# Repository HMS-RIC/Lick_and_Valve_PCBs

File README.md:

# Lick Sensor and Valve Driver PCBs

Two useful PCBs:

- A two channel resistive lick sensor.

- An eight channel valve driver with the option of automatic operation with a microcontroller (Teensy).

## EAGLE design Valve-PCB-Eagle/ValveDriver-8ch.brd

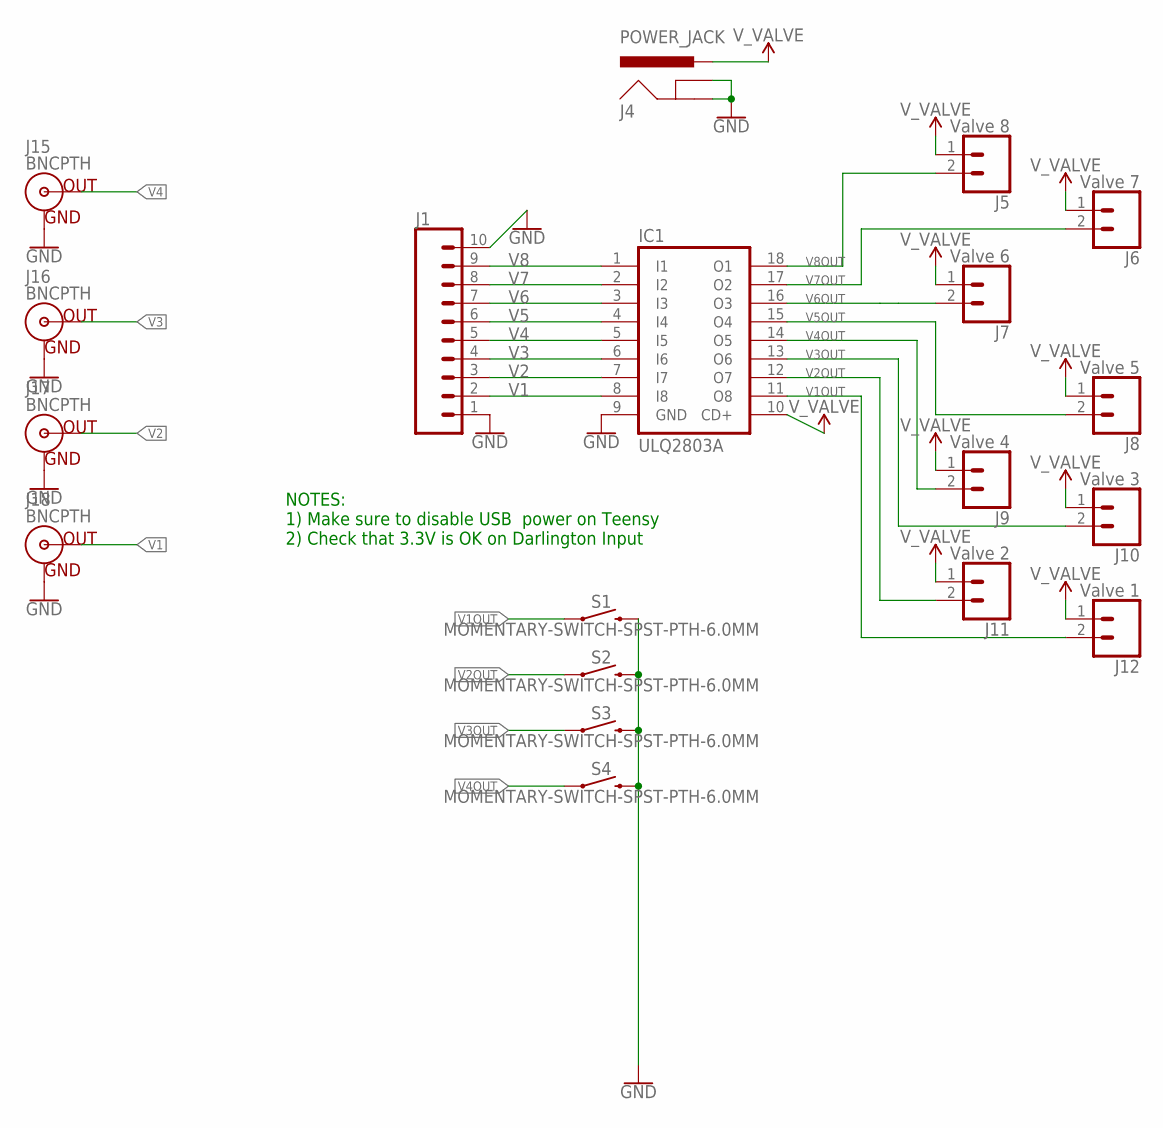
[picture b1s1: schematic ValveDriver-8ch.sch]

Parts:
IC1: ULQ2803A; DIL18
J1: CONN_10"; 1X10
J4: POWER_JACK; POWER_JACK_PTH
J5: Valve 8; 1X02
J6: Valve 7; 1X02
J7: Valve 6; 1X02
J8: Valve 5; 1X02
J9: Valve 4; 1X02
J10: Valve 3; 1X02
J11: Valve 2; 1X02
J12: Valve 1; 1X02
J15, J16, J17, J18: BNCPTH; BNC
S1, S2, S3, S4: MOMENTARY-SWITCH-SPST-PTH-6.0MM; TACTILE_SWITCH_PTH_6.0MM

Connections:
GND: IC1.9 (GND), J1.1, J1.10, J4.GND, J4.GNDBREAK, J15.GND, J16.GND, J17.GND, J18.GND, S1.3 (2), S2.3 (2), S3.3 (2), S4.3 (2)
V1: IC1.8 (I8), J1.2, J18.S (OUT)
V1OUT: IC1.11 (O8), J12.2, S1.1
V2: IC1.7 (I7), J1.3, J17.S (OUT)
V2OUT: IC1.12 (O7), J11.2, S2.1
V3: IC1.6 (I6), J1.4, J16.S (OUT)
V3OUT: IC1.13 (O6), J10.2, S3.1
V4: IC1.5 (I5), J1.5, J15.S (OUT)
V4OUT: IC1.14 (O5), J9.2, S4.1
V5: IC1.4 (I4), J1.6
V5OUT: IC1.15 (O4), J8.2
V6: IC1.3 (I3), J1.7
V6OUT: IC1.16 (O3), J7.2
V7: IC1.2 (I2), J1.8
V7OUT: IC1.17 (O2), J6.2
V8: IC1.1 (I1), J1.9
V8OUT: IC1.18 (O1), J5.2
V_VALVE: IC1.10 (CD+), J4.PWR, J5.1, J6.1, J7.1, J8.1, J9.1, J10.1, J11.1, J12.1

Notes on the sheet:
NOTES: 1) Make sure to disable USB power on Teensy 2) Check that 3.3V is OK on Darlington Input

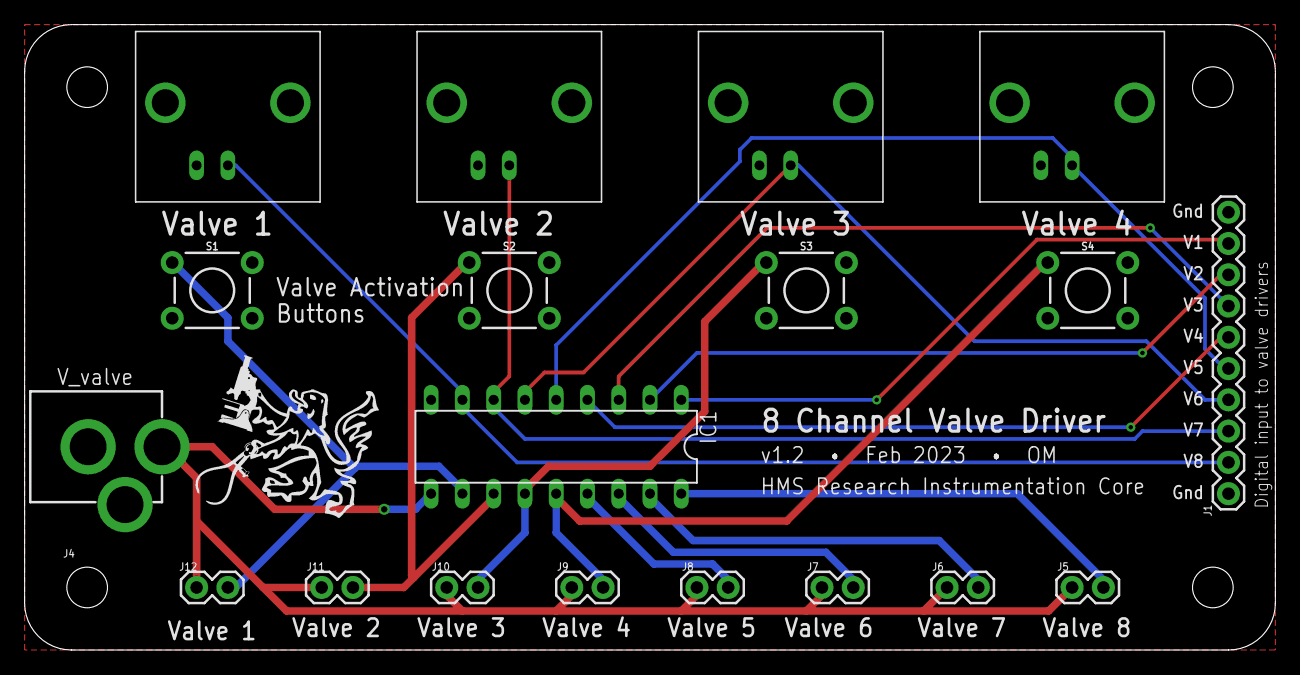
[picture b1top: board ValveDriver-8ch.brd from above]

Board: 2 copper layers, 101.6 x 50.8 mm, 24 parts (0 on the bottom side), 18 nets.

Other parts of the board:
U$2, U$4, U$5, U$6: STAND-OFF
U$7: RIC_LOGO_BIG

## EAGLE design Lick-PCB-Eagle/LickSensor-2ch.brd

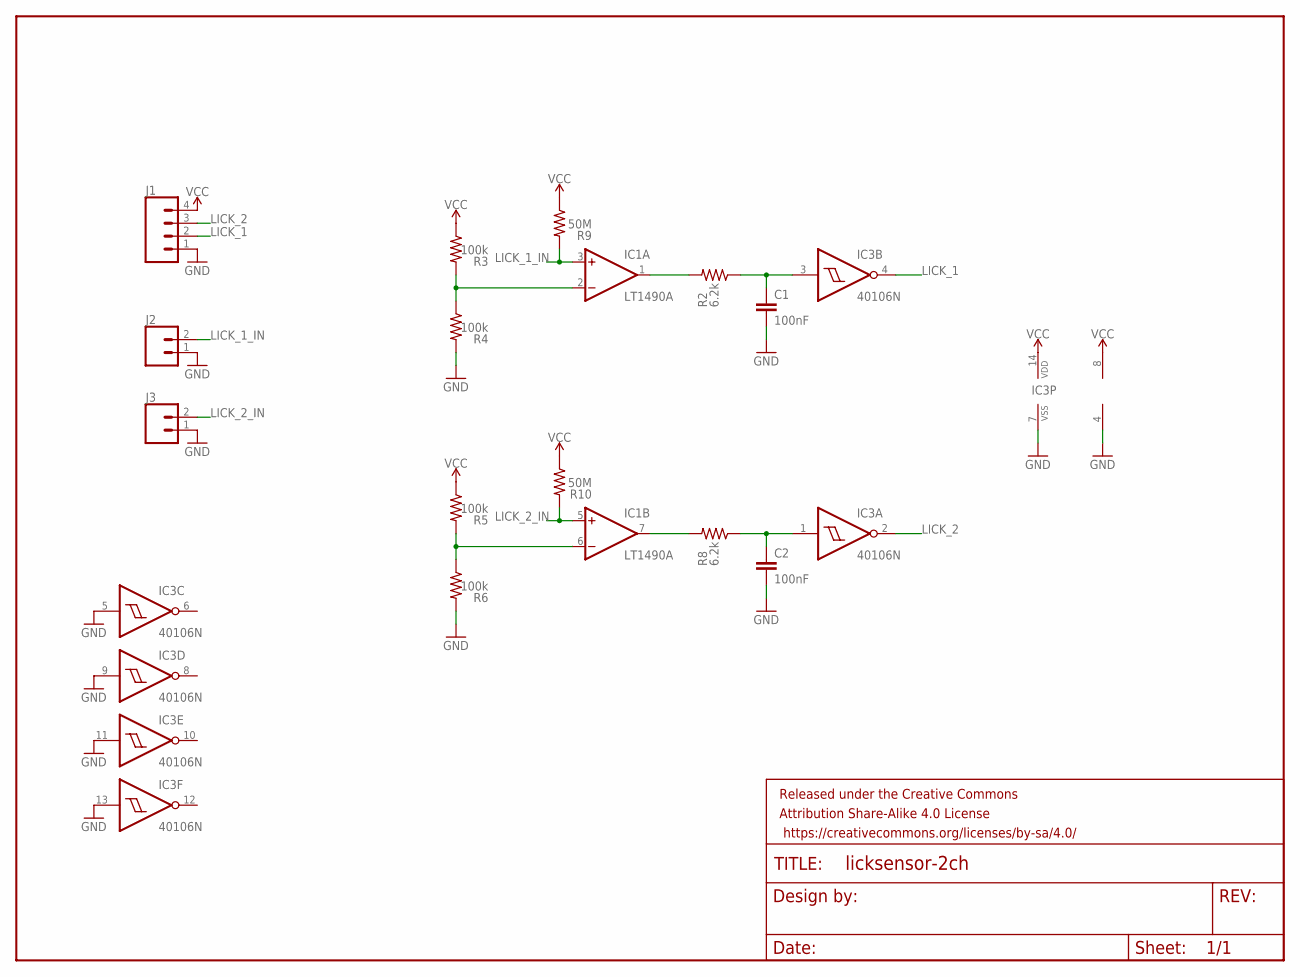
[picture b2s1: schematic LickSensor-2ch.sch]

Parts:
C1, C2: 100nF; C5B3
FRAME1: FRAME-LETTER; CREATIVE_COMMONS
IC1: LT1490A; DIL08
IC3: 40106N; DIL14
J1: CONN_04; 1X04
J2, J3: CONN_02; 1X02
R2, R8: 6.2k; AXIAL-0.5
R3, R4, R5, R6: 100k; AXIAL-0.5
R9, R10: 50M; AXIAL-0.5

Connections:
GND: C1.2, C2.2, IC1.4 (V-), IC3.5 (I), IC3.7 (VSS), IC3.9 (I), IC3.11 (I), IC3.13 (I), J1.1, J2.1, J3.1, R4.P$2 (2), R6.P$2 (2)
LICK_1: IC3.4 (O), J1.2
LICK_1_IN: IC1.3 (+IN), J2.2, R9.P$2 (2)
LICK_2: IC3.2 (O), J1.3
LICK_2_IN: IC1.5 (+IN), J3.2, R10.P$2 (2)
unnamed: C1.1, IC3.3 (I), R2.P$1 (1)
unnamed: IC1.1 (OUT), R2.P$2 (2)
unnamed: IC1.2 (-IN), R3.P$2 (2), R4.P$1 (1)
unnamed: IC1.6 (-IN), R5.P$2 (2), R6.P$1 (1)
unnamed: C2.1, IC3.1 (I), R8.P$1 (1)
unnamed: IC1.7 (OUT), R8.P$2 (2)
VCC: IC1.8 (V+), IC3.14 (VDD), J1.4, R3.P$1 (1), R5.P$1 (1), R9.P$1 (1), R10.P$1 (1)

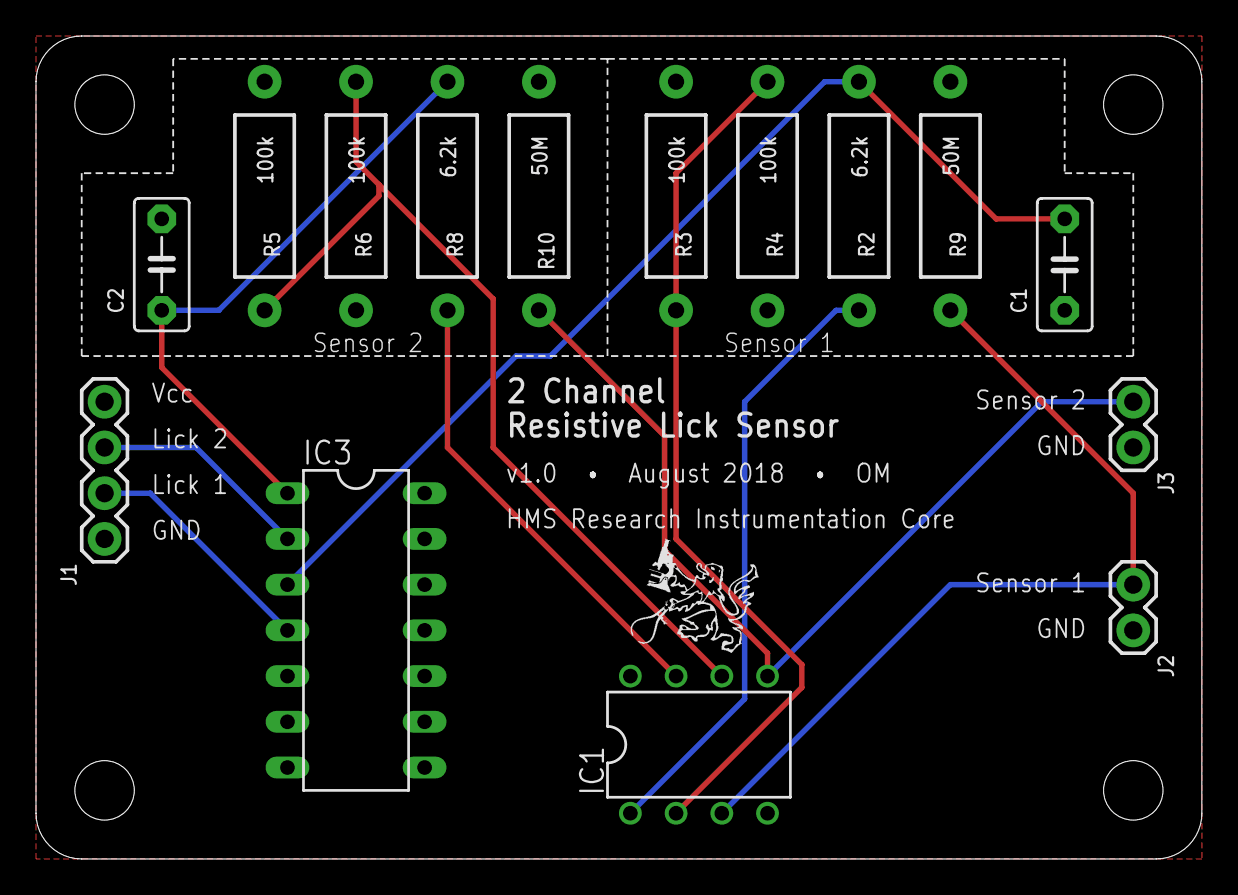
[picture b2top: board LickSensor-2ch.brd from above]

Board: 2 copper layers, 64.8 x 45.7 mm, 21 parts (0 on the bottom side), 12 nets.

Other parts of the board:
U$1, U$2, U$3, U$4: STAND-OFF
U$5: RIC_LOGO_SMALL

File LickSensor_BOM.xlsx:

Part | Value | Device | Digikey part | Unit Price (@qty=10) | Notes
IC1 |  | LT1490A | LT1490AIN8#PBF-ND | 4.6100000000000003
IC3 |  | CD40106B | 296-3503-5-ND | 0.44
J1 |  | CONN_04 |  |  | 0.1" header or socket (4 pin)
J2 |  | CONN_02 |  |  | 0.1" header or socket (2 pin)
J3 |  | CONN_02 |  |  | 0.1" header or socket (2 pin)
R2 | 6.2k | Resistor
R3 | 100k | Resistor
R4 | 100k | Resistor
R5 | 100k | Resistor
R6 | 100k | Resistor
R8 | 6.2k | Resistor
R9 | 50M | Resistor
R10 | 50M | Resistor
C1 | 100nF | CAPACITOR
C2 | 100nF | CAPACITOR

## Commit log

2018-08-23 Add example Teensy code for valve driver board
2018-09-28 [Teensy] Move pin information to header file
2018-09-28 [Valve][Teensy] Fix mistaken labeling of Lick1/Lick2 pins
2018-11-15 [Lick] Add datasheets for ICs
2019-01-29 [Valve] Add 5V to screw term (fixes #6)
2019-01-30 [Valve] Make minor tweaks to board size & layout
2019-01-30 [Valve] Add valve manifold connection
2019-02-04 [Valve] Add momentary push buttons (fixes #1)
2023-02-23 [Valve] Add board pdf
2023-02-23 [Valve] Silkscreen improvements
2023-02-24 [Valve] Remove manifold; remove buttons 5–8; make PCB more compact
2023-02-24 [Valve] Removed Teensy and associated I/O connections
2023-02-24 [Valve] Fix silkscreen layer issue

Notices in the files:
parts and their libraries:
SparkFun-Connectors: Licensing: Creative Commons ShareAlike 4.0 International - https://creativecommons.org/licenses/by-sa/4.0
SparkFun-Aesthetics: Released under the Creative Commons Attribution Share-Alike 4.0 License
SparkFun-Aesthetics: https://creativecommons.org/licenses/by-sa/4.0
